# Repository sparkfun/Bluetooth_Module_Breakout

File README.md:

SparkFun Bluetooth Module Breakout - RN41
==========================================

[*SparkFun Bluetooth Module Breakout-RN41 (WRL-12579)*](https://www.sparkfun.com/products/12579)

This is a simple breakout for the Roving Networks RN41 Bluetooth module. 

Repository Contents
-------------------
* **/Hardware** - All Eagle design files (.brd, .sch)
* **/Production** - Test bed files and production panel files

Product Versions
----------------
* [WRL-12579](https://www.sparkfun.com/products/12579)- Version 1.5. Current. 
* [WRL-10559](https://www.sparkfun.com/products/retired/10559)- Version 1.4. Retired.

Version History
---------------
* [V_1.5](https://github.com/sparkfun/Bluetooth_Module_Breakout/tree/V_1.5) - GitHub files for version 1.5. 
* [V_1.4](https://github.com/sparkfun/Bluetooth_Module_Breakout/tree/V_1.4) -GitHub files for version 1.4.

License Information
-------------------
The hardware is released under [Creative Commons ShareAlike 4.0 International](https://creativecommons.org/licenses/by-sa/4.0/).

Distributed as-is; no warranty is given.

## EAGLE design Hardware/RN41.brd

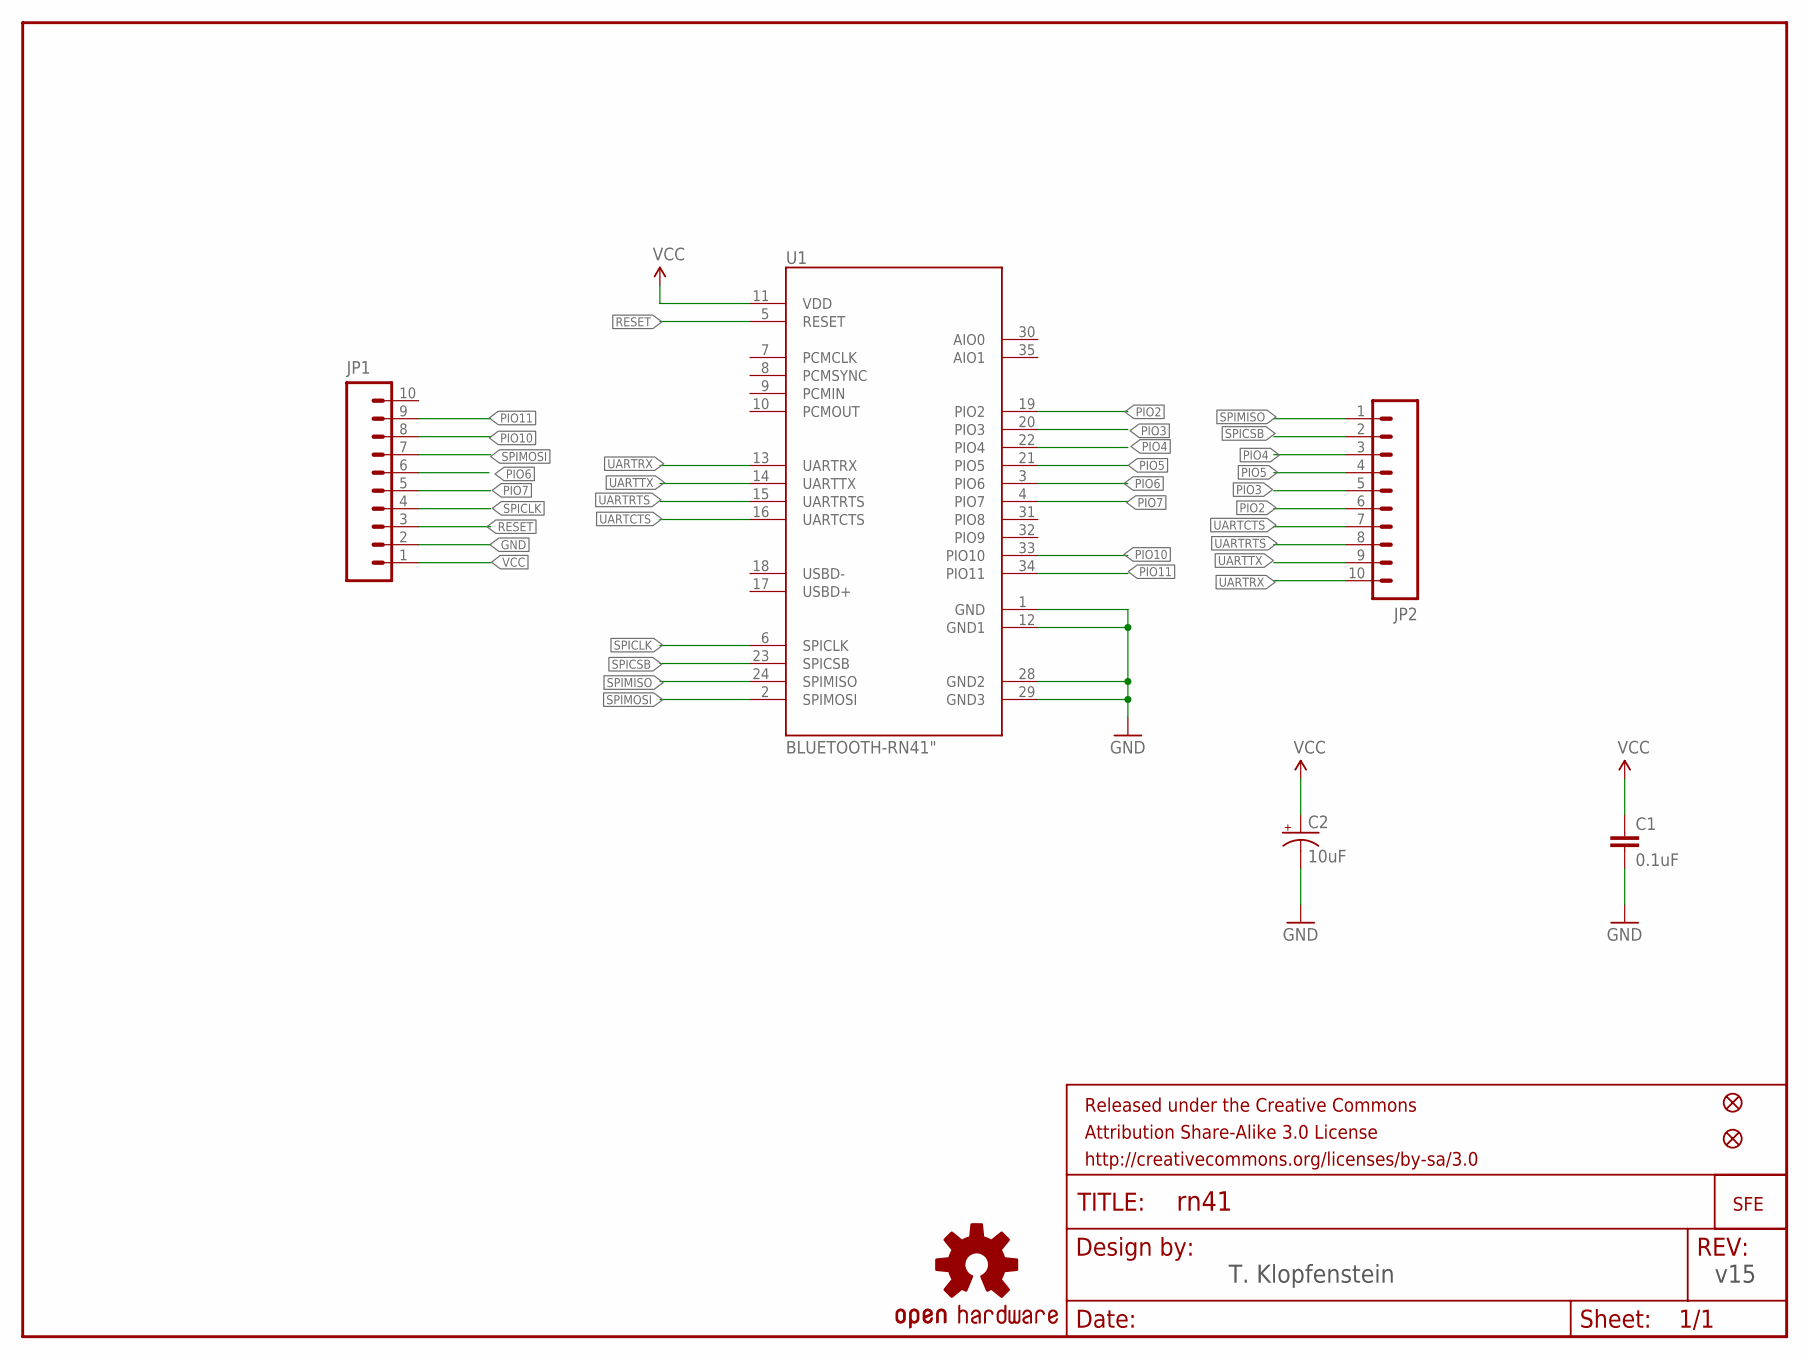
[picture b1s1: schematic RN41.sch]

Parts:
C1: 0.1uF; 0603-CAP
C2: 10uF; EIA3216
FID1, FID2: FIDUCIALUFIDUCIAL; MICRO-FIDUCIAL
FRAME1: FRAME-LETTER; CREATIVE_COMMONS
JP1, JP2: M10"; 1X10
LOGO1: OSHW-LOGOS; OSHW-LOGO-S
U1: BLUETOOTH-RN41"; RN41
U$1: LOGO-SFENEW; SFE-NEW-WEBLOGO

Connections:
GND: C1.2, C2.C (-), JP1.2, U1.1 (GND), U1.12 (GND1), U1.28 (GND2), U1.29 (GND3)
PIO2: JP2.6, U1.19 (PIO2)
PIO3: JP2.5, U1.20 (PIO3)
PIO4: JP2.3, U1.22 (PIO4)
PIO5: JP2.4, U1.21 (PIO5)
PIO6: JP1.6, U1.3 (PIO6)
PIO7: JP1.5, U1.4 (PIO7)
PIO10: JP1.8, U1.33 (PIO10)
PIO11: JP1.9, U1.34 (PIO11)
RESET: JP1.3, U1.5 (RESET)
SPICLK: JP1.4, U1.6 (SPICLK)
SPICSB: JP2.2, U1.23 (SPICSB)
SPIMISO: JP2.1, U1.24 (SPIMISO)
SPIMOSI: JP1.7, U1.2 (SPIMOSI)
UARTCTS: JP2.7, U1.16 (UARTCTS)
UARTRTS: JP2.8, U1.15 (UARTRTS)
UARTRX: JP2.10, U1.13 (UARTRX)
UARTTX: JP2.9, U1.14 (UARTTX)
VCC: C1.1, C2.A (+), JP1.1, U1.11 (VDD)

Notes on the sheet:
v15
T. Klopfenstein

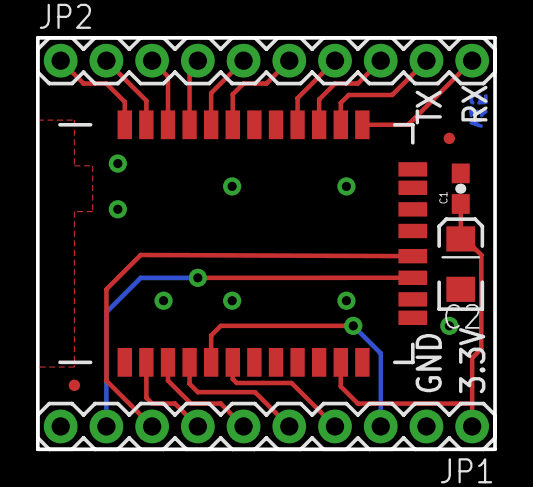
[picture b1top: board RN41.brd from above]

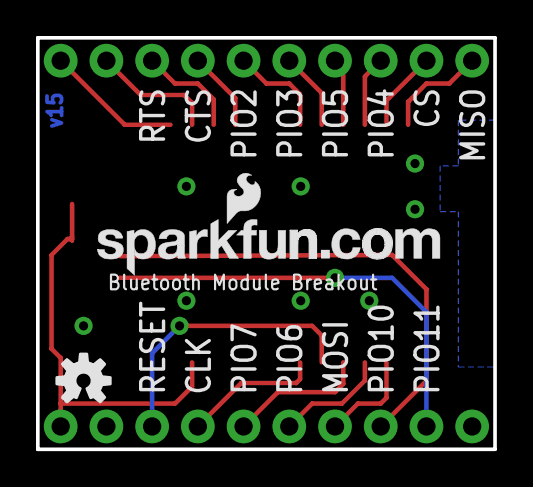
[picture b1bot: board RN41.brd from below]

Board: 2 copper layers, 25.4 x 22.9 mm, 10 parts (2 on the bottom side), 19 nets.

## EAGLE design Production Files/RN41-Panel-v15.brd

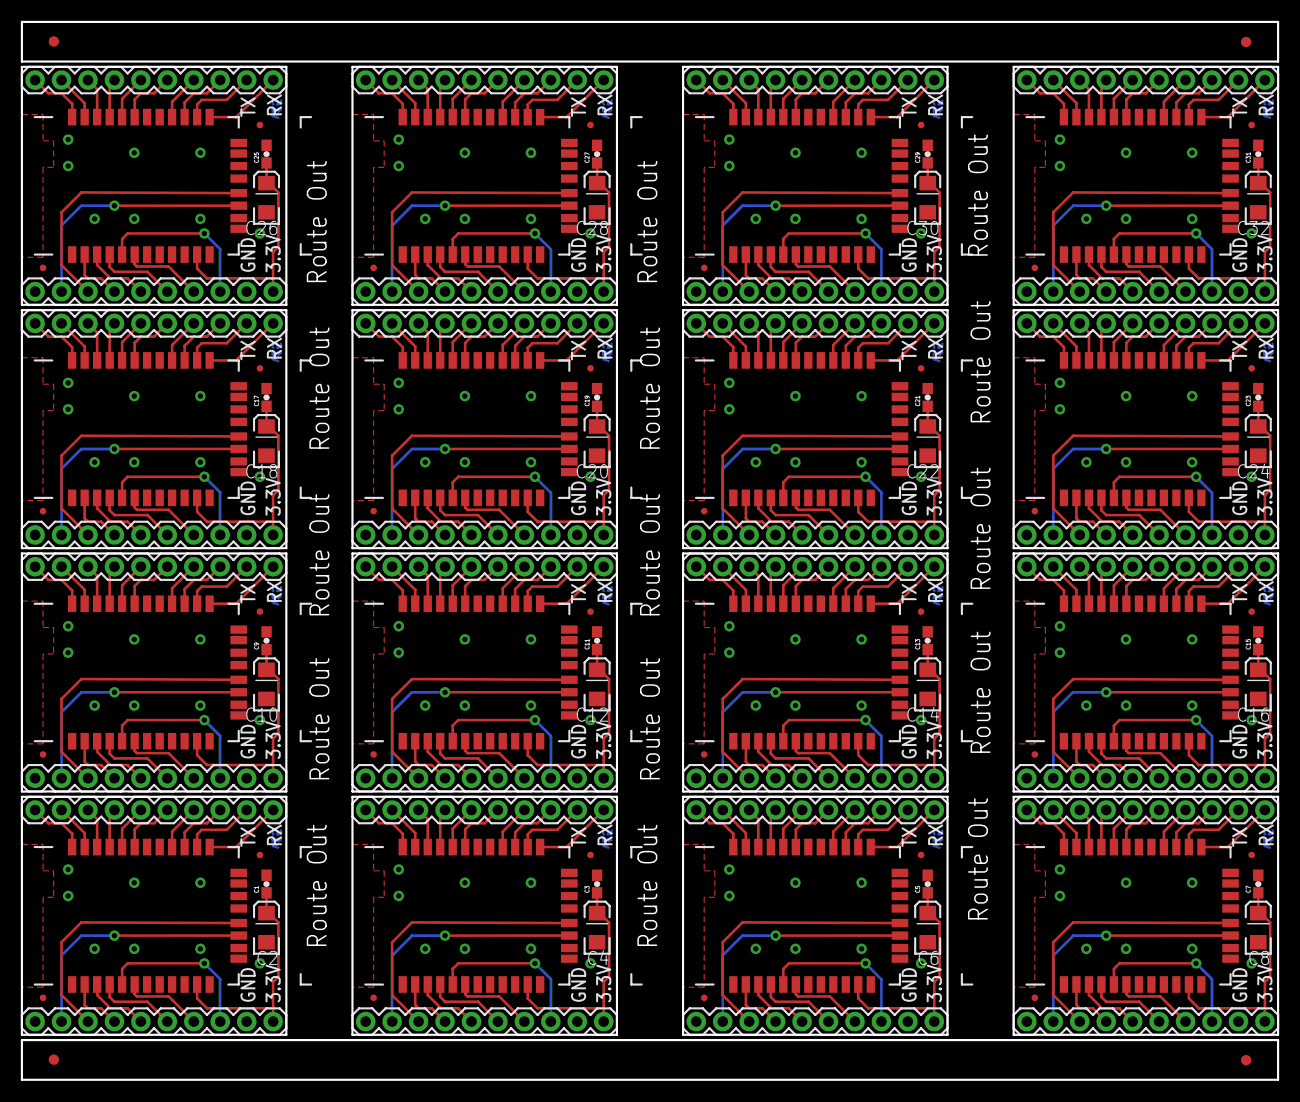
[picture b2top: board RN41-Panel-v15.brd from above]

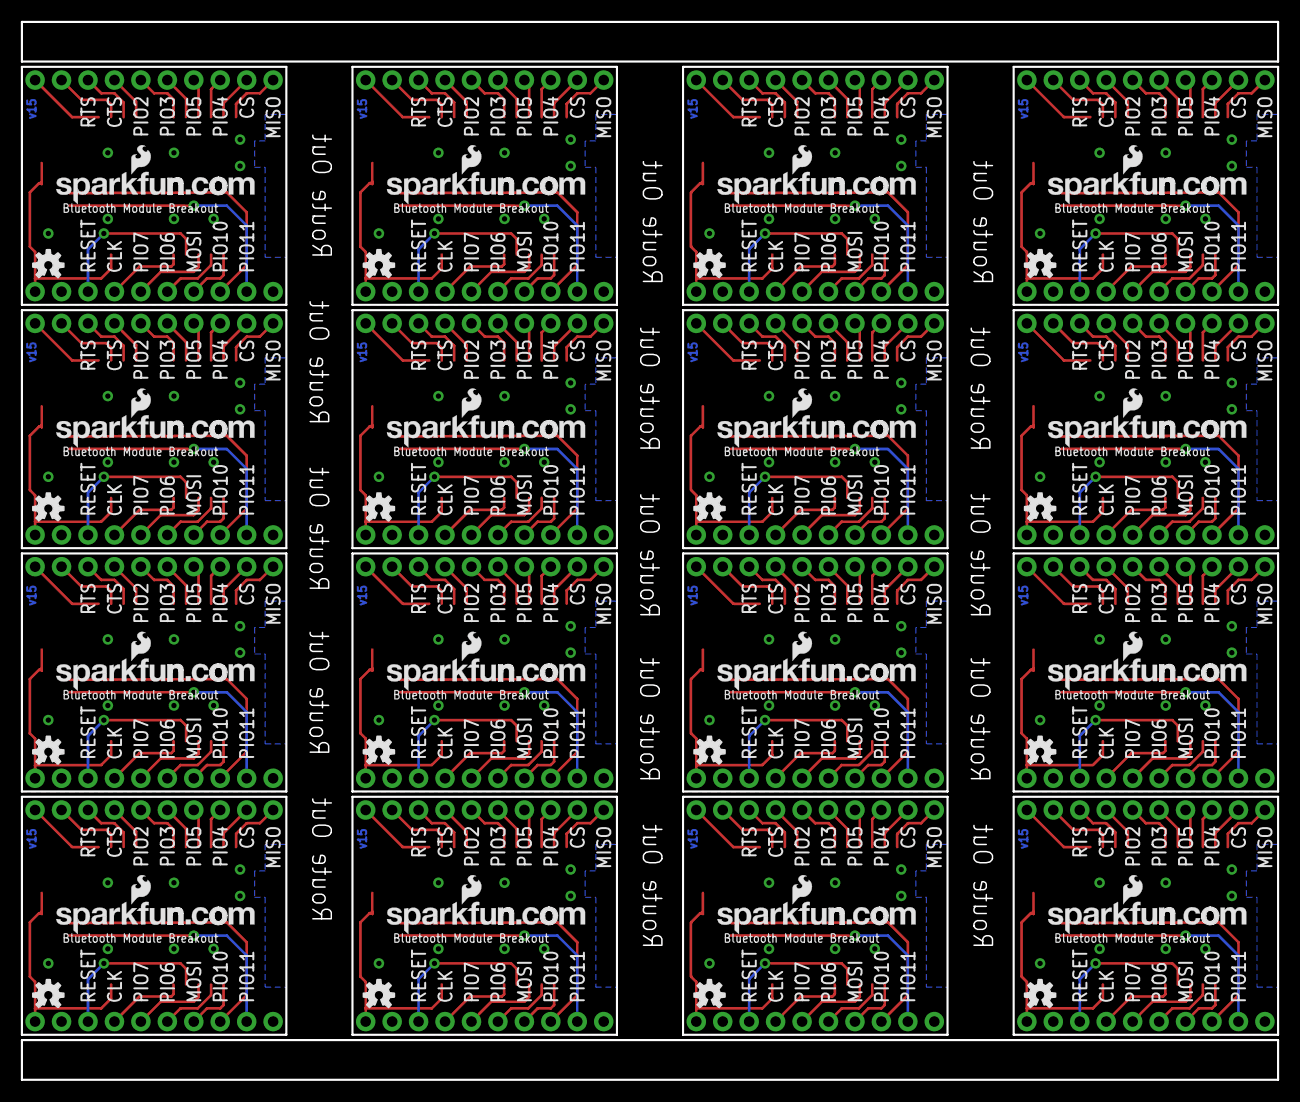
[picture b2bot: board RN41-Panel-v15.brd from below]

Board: 2 copper layers, 120.7 x 101.6 mm, 148 parts (32 on the bottom side), 304 nets.

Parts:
C1, C3, C5, C7, C9, C11, C13, C15, C17, C19, C21, C23, C25, C27, C29, C31: 0.1uF; 0603-CAP
C2, C4, C6, C8, C10, C12, C14, C16, C18, C20, C22, C24, C26, C28, C30, C32: 10uF; EIA3216
E$1, E$2, E$3, E$4: FIDUCIAL-1X2
FID1, FID2, FID3, FID4, FID5, FID6, FID7, FID8, FID9, FID10, FID11, FID12, FID13, FID14, FID15, FID16, FID17, FID18, FID19, FID20, FID21, FID22, FID23, FID24, FID25, FID26, FID27, FID28, FID29, FID30, FID31, FID32: FIDUCIALUFIDUCIAL; MICRO-FIDUCIAL
JP1, JP2, JP3, JP4, JP5, JP6, JP7, JP8, JP9, JP10, JP11, JP12, JP13, JP14, JP15, JP16, JP17, JP18, JP19, JP20, JP21, JP22, JP23, JP24, JP25, JP26, JP27, JP28, JP29, JP30, JP31, JP32: 1X10
LOGO1, LOGO2, LOGO3, LOGO4, LOGO5, LOGO6, LOGO7, LOGO8, LOGO9, LOGO10, LOGO11, LOGO12, LOGO13, LOGO14, LOGO15, LOGO16: OSHW-LOGOS; OSHW-LOGO-S
U1, U2, U3, U4, U5, U6, U7, U8, U9, U10, U11, U12, U13, U14, U15, U16: BLUETOOTH-RN41"; RN41
U$1, U$2, U$3, U$4, U$5, U$6, U$7, U$8, U$9, U$10, U$11, U$12, U$13, U$14, U$15, U$16: LOGO-SFENEW; SFE-NEW-WEBLOGO

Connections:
GND: C1.2, C2.C, JP1.2, U1.1, U1.12, U1.28, U1.29
GND1: C3.2, C4.C, JP3.2, U2.1, U2.12, U2.28, U2.29
GND2: C5.2, C6.C, JP5.2, U3.1, U3.12, U3.28, U3.29
GND3: C7.2, C8.C, JP7.2, U4.1, U4.12, U4.28, U4.29
GND4: C9.2, C10.C, JP9.2, U5.1, U5.12, U5.28, U5.29
GND5: C11.2, C12.C, JP11.2, U6.1, U6.12, U6.28, U6.29
GND6: C13.2, C14.C, JP13.2, U7.1, U7.12, U7.28, U7.29
GND7: C15.2, C16.C, JP15.2, U8.1, U8.12, U8.28, U8.29
GND8: C17.2, C18.C, JP17.2, U9.1, U9.12, U9.28, U9.29
GND9: C19.2, C20.C, JP19.2, U10.1, U10.12, U10.28, U10.29
GND10: C21.2, C22.C, JP21.2, U11.1, U11.12, U11.28, U11.29
GND11: C23.2, C24.C, JP23.2, U12.1, U12.12, U12.28, U12.29
GND12: C25.2, C26.C, JP25.2, U13.1, U13.12, U13.28, U13.29
GND13: C27.2, C28.C, JP27.2, U14.1, U14.12, U14.28, U14.29
GND14: C29.2, C30.C, JP29.2, U15.1, U15.12, U15.28, U15.29
GND15: C31.2, C32.C, JP31.2, U16.1, U16.12, U16.28, U16.29
PIO1: JP4.6, U2.19
PIO2: JP2.6, U1.19
PIO3: JP2.5, U1.20
PIO4: JP2.3, U1.22
PIO5: JP2.4, U1.21
PIO6: JP1.6, U1.3
PIO7: JP1.5, U1.4
PIO8: JP4.5, U2.20
PIO9: JP4.3, U2.22
PIO10: JP1.8, U1.33
PIO11: JP1.9, U1.34
PIO12: JP4.4, U2.21
PIO13: JP3.6, U2.3
PIO14: JP3.5, U2.4
PIO15: JP3.8, U2.33
PIO16: JP3.9, U2.34
PIO17: JP6.6, U3.19
PIO18: JP6.5, U3.20
PIO19: JP6.3, U3.22
PIO20: JP6.4, U3.21
PIO21: JP5.6, U3.3
PIO22: JP5.5, U3.4
PIO23: JP5.8, U3.33
PIO24: JP5.9, U3.34
PIO25: JP8.6, U4.19
PIO26: JP8.5, U4.20
PIO27: JP8.3, U4.22
PIO28: JP8.4, U4.21
PIO29: JP7.6, U4.3
PIO30: JP7.5, U4.4
PIO31: JP7.8, U4.33
PIO32: JP7.9, U4.34
PIO33: JP10.6, U5.19
PIO34: JP10.5, U5.20
PIO35: JP10.3, U5.22
PIO36: JP10.4, U5.21
PIO37: JP9.6, U5.3
PIO38: JP9.5, U5.4
PIO39: JP9.8, U5.33
PIO40: JP9.9, U5.34
PIO41: JP12.6, U6.19
PIO42: JP12.5, U6.20
PIO43: JP12.3, U6.22
PIO44: JP12.4, U6.21
PIO45: JP11.6, U6.3
PIO46: JP11.5, U6.4
PIO47: JP11.8, U6.33
PIO48: JP11.9, U6.34
PIO49: JP14.6, U7.19
PIO50: JP14.5, U7.20
PIO51: JP14.3, U7.22
PIO52: JP14.4, U7.21
PIO53: JP13.6, U7.3
PIO54: JP13.5, U7.4
PIO55: JP13.8, U7.33
PIO56: JP13.9, U7.34
PIO57: JP16.6, U8.19
PIO58: JP16.5, U8.20
PIO59: JP16.3, U8.22
PIO60: JP16.4, U8.21
PIO61: JP15.6, U8.3
PIO62: JP15.5, U8.4
PIO63: JP15.8, U8.33
PIO64: JP15.9, U8.34
PIO65: JP18.6, U9.19
PIO66: JP18.5, U9.20
PIO67: JP18.3, U9.22
PIO68: JP18.4, U9.21
PIO69: JP17.6, U9.3
PIO70: JP17.5, U9.4
PIO71: JP17.8, U9.33
PIO72: JP17.9, U9.34
PIO73: JP20.6, U10.19
PIO74: JP20.5, U10.20
PIO75: JP20.3, U10.22
PIO76: JP20.4, U10.21
PIO77: JP19.6, U10.3
PIO78: JP19.5, U10.4
PIO79: JP19.8, U10.33
PIO80: JP19.9, U10.34
PIO81: JP22.6, U11.19
PIO82: JP22.5, U11.20
PIO83: JP22.3, U11.22
PIO84: JP22.4, U11.21
PIO85: JP21.6, U11.3
PIO86: JP21.5, U11.4
PIO87: JP21.8, U11.33
PIO88: JP21.9, U11.34
PIO89: JP24.6, U12.19
PIO90: JP24.5, U12.20
PIO91: JP24.3, U12.22
PIO92: JP24.4, U12.21
PIO93: JP23.6, U12.3
PIO94: JP23.5, U12.4
PIO95: JP23.8, U12.33
PIO96: JP23.9, U12.34
PIO97: JP26.6, U13.19
PIO98: JP26.5, U13.20
PIO99: JP26.3, U13.22
PIO100: JP26.4, U13.21
PIO101: JP25.6, U13.3
PIO102: JP25.5, U13.4
PIO103: JP25.8, U13.33
PIO104: JP25.9, U13.34
PIO105: JP28.6, U14.19
PIO106: JP28.5, U14.20
PIO107: JP28.3, U14.22
PIO108: JP28.4, U14.21
PIO109: JP27.6, U14.3
PIO110: JP27.5, U14.4
PIO111: JP27.8, U14.33
PIO112: JP27.9, U14.34
PIO113: JP30.6, U15.19
PIO114: JP30.5, U15.20
PIO115: JP30.3, U15.22
PIO116: JP30.4, U15.21
PIO117: JP29.6, U15.3
PIO118: JP29.5, U15.4
PIO119: JP29.8, U15.33
PIO120: JP29.9, U15.34
PIO121: JP32.6, U16.19
PIO122: JP32.5, U16.20
PIO123: JP32.3, U16.22
PIO124: JP32.4, U16.21
PIO125: JP31.6, U16.3
PIO126: JP31.5, U16.4
PIO127: JP31.8, U16.33
PIO128: JP31.9, U16.34
RESET: JP1.3, U1.5
RESET1: JP3.3, U2.5
RESET2: JP5.3, U3.5
RESET3: JP7.3, U4.5
RESET4: JP9.3, U5.5
RESET5: JP11.3, U6.5
RESET6: JP13.3, U7.5
RESET7: JP15.3, U8.5
RESET8: JP17.3, U9.5
RESET9: JP19.3, U10.5
RESET10: JP21.3, U11.5
RESET11: JP23.3, U12.5
RESET12: JP25.3, U13.5
RESET13: JP27.3, U14.5
RESET14: JP29.3, U15.5
RESET15: JP31.3, U16.5
SPICLK: JP1.4, U1.6
SPICLK1: JP3.4, U2.6
SPICLK2: JP5.4, U3.6
SPICLK3: JP7.4, U4.6
SPICLK4: JP9.4, U5.6
SPICLK5: JP11.4, U6.6
SPICLK6: JP13.4, U7.6
SPICLK7: JP15.4, U8.6
SPICLK8: JP17.4, U9.6
SPICLK9: JP19.4, U10.6
SPICLK10: JP21.4, U11.6
SPICLK11: JP23.4, U12.6
SPICLK12: JP25.4, U13.6
SPICLK13: JP27.4, U14.6
SPICLK14: JP29.4, U15.6
SPICLK15: JP31.4, U16.6
SPICSB: JP2.2, U1.23
SPICSB1: JP4.2, U2.23
SPICSB2: JP6.2, U3.23
SPICSB3: JP8.2, U4.23
SPICSB4: JP10.2, U5.23
SPICSB5: JP12.2, U6.23
SPICSB6: JP14.2, U7.23
SPICSB7: JP16.2, U8.23
SPICSB8: JP18.2, U9.23
SPICSB9: JP20.2, U10.23
SPICSB10: JP22.2, U11.23
SPICSB11: JP24.2, U12.23
SPICSB12: JP26.2, U13.23
SPICSB13: JP28.2, U14.23
SPICSB14: JP30.2, U15.23
SPICSB15: JP32.2, U16.23
SPIMISO: JP2.1, U1.24
SPIMISO1: JP4.1, U2.24
SPIMISO2: JP6.1, U3.24
SPIMISO3: JP8.1, U4.24
SPIMISO4: JP10.1, U5.24
SPIMISO5: JP12.1, U6.24
SPIMISO6: JP14.1, U7.24
SPIMISO7: JP16.1, U8.24
SPIMISO8: JP18.1, U9.24
SPIMISO9: JP20.1, U10.24
SPIMISO10: JP22.1, U11.24
SPIMISO11: JP24.1, U12.24
SPIMISO12: JP26.1, U13.24
SPIMISO13: JP28.1, U14.24
SPIMISO14: JP30.1, U15.24
SPIMISO15: JP32.1, U16.24
SPIMOSI: JP1.7, U1.2
SPIMOSI1: JP3.7, U2.2
SPIMOSI2: JP5.7, U3.2
SPIMOSI3: JP7.7, U4.2
SPIMOSI4: JP9.7, U5.2
SPIMOSI5: JP11.7, U6.2
SPIMOSI6: JP13.7, U7.2
SPIMOSI7: JP15.7, U8.2
SPIMOSI8: JP17.7, U9.2
SPIMOSI9: JP19.7, U10.2
SPIMOSI10: JP21.7, U11.2
SPIMOSI11: JP23.7, U12.2
SPIMOSI12: JP25.7, U13.2
SPIMOSI13: JP27.7, U14.2
SPIMOSI14: JP29.7, U15.2
SPIMOSI15: JP31.7, U16.2
UARTCTS: JP2.7, U1.16
UARTCTS1: JP4.7, U2.16
UARTCTS2: JP6.7, U3.16
UARTCTS3: JP8.7, U4.16
UARTCTS4: JP10.7, U5.16
UARTCTS5: JP12.7, U6.16
UARTCTS6: JP14.7, U7.16
UARTCTS7: JP16.7, U8.16
UARTCTS8: JP18.7, U9.16
UARTCTS9: JP20.7, U10.16
UARTCTS10: JP22.7, U11.16
UARTCTS11: JP24.7, U12.16
UARTCTS12: JP26.7, U13.16
UARTCTS13: JP28.7, U14.16
UARTCTS14: JP30.7, U15.16
UARTCTS15: JP32.7, U16.16
UARTRTS: JP2.8, U1.15
UARTRTS1: JP4.8, U2.15
UARTRTS2: JP6.8, U3.15
UARTRTS3: JP8.8, U4.15
UARTRTS4: JP10.8, U5.15
UARTRTS5: JP12.8, U6.15
UARTRTS6: JP14.8, U7.15
UARTRTS7: JP16.8, U8.15
UARTRTS8: JP18.8, U9.15
UARTRTS9: JP20.8, U10.15
UARTRTS10: JP22.8, U11.15
UARTRTS11: JP24.8, U12.15
UARTRTS12: JP26.8, U13.15
UARTRTS13: JP28.8, U14.15
UARTRTS14: JP30.8, U15.15
UARTRTS15: JP32.8, U16.15
UARTRX: JP2.10, U1.13
UARTRX1: JP4.10, U2.13
UARTRX2: JP6.10, U3.13
UARTRX3: JP8.10, U4.13
UARTRX4: JP10.10, U5.13
UARTRX5: JP12.10, U6.13
UARTRX6: JP14.10, U7.13
UARTRX7: JP16.10, U8.13
UARTRX8: JP18.10, U9.13
UARTRX9: JP20.10, U10.13
UARTRX10: JP22.10, U11.13
UARTRX11: JP24.10, U12.13
UARTRX12: JP26.10, U13.13
UARTRX13: JP28.10, U14.13
UARTRX14: JP30.10, U15.13
UARTRX15: JP32.10, U16.13
UARTTX: JP2.9, U1.14
UARTTX1: JP4.9, U2.14
UARTTX2: JP6.9, U3.14
UARTTX3: JP8.9, U4.14
UARTTX4: JP10.9, U5.14
UARTTX5: JP12.9, U6.14
UARTTX6: JP14.9, U7.14
UARTTX7: JP16.9, U8.14
UARTTX8: JP18.9, U9.14
UARTTX9: JP20.9, U10.14
UARTTX10: JP22.9, U11.14
UARTTX11: JP24.9, U12.14
UARTTX12: JP26.9, U13.14
UARTTX13: JP28.9, U14.14
UARTTX14: JP30.9, U15.14
UARTTX15: JP32.9, U16.14
VCC: C1.1, C2.A, JP1.1, U1.11
VCC1: C3.1, C4.A, JP3.1, U2.11
VCC2: C5.1, C6.A, JP5.1, U3.11
VCC3: C7.1, C8.A, JP7.1, U4.11
VCC4: C9.1, C10.A, JP9.1, U5.11
VCC5: C11.1, C12.A, JP11.1, U6.11
VCC6: C13.1, C14.A, JP13.1, U7.11
VCC7: C15.1, C16.A, JP15.1, U8.11
VCC8: C17.1, C18.A, JP17.1, U9.11
VCC9: C19.1, C20.A, JP19.1, U10.11
VCC10: C21.1, C22.A, JP21.1, U11.11
VCC11: C23.1, C24.A, JP23.1, U12.11
VCC12: C25.1, C26.A, JP25.1, U13.11
VCC13: C27.1, C28.A, JP27.1, U14.11
VCC14: C29.1, C30.A, JP29.1, U15.11
VCC15: C31.1, C32.A, JP31.1, U16.11

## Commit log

2013-06-06 Initial file commit
2013-06-11 Adding board name to silk screen
2013-06-12 Production ready v15
    Added fiducials and created panel
2014-01-21 Fixing to current board files
2015-02-13 Updating README with new product info links

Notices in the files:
parts and their libraries:
SparkFun-Aesthetics: Licensing: CC v3.0 Share-Alike You are welcome to use this library for commercial purposes.
SparkFun-Aesthetics: Released under the Creative Commons Attribution Share-Alike 3.0 License
SparkFun-Aesthetics: http://creativecommons.org/licenses/by-sa/3.0
